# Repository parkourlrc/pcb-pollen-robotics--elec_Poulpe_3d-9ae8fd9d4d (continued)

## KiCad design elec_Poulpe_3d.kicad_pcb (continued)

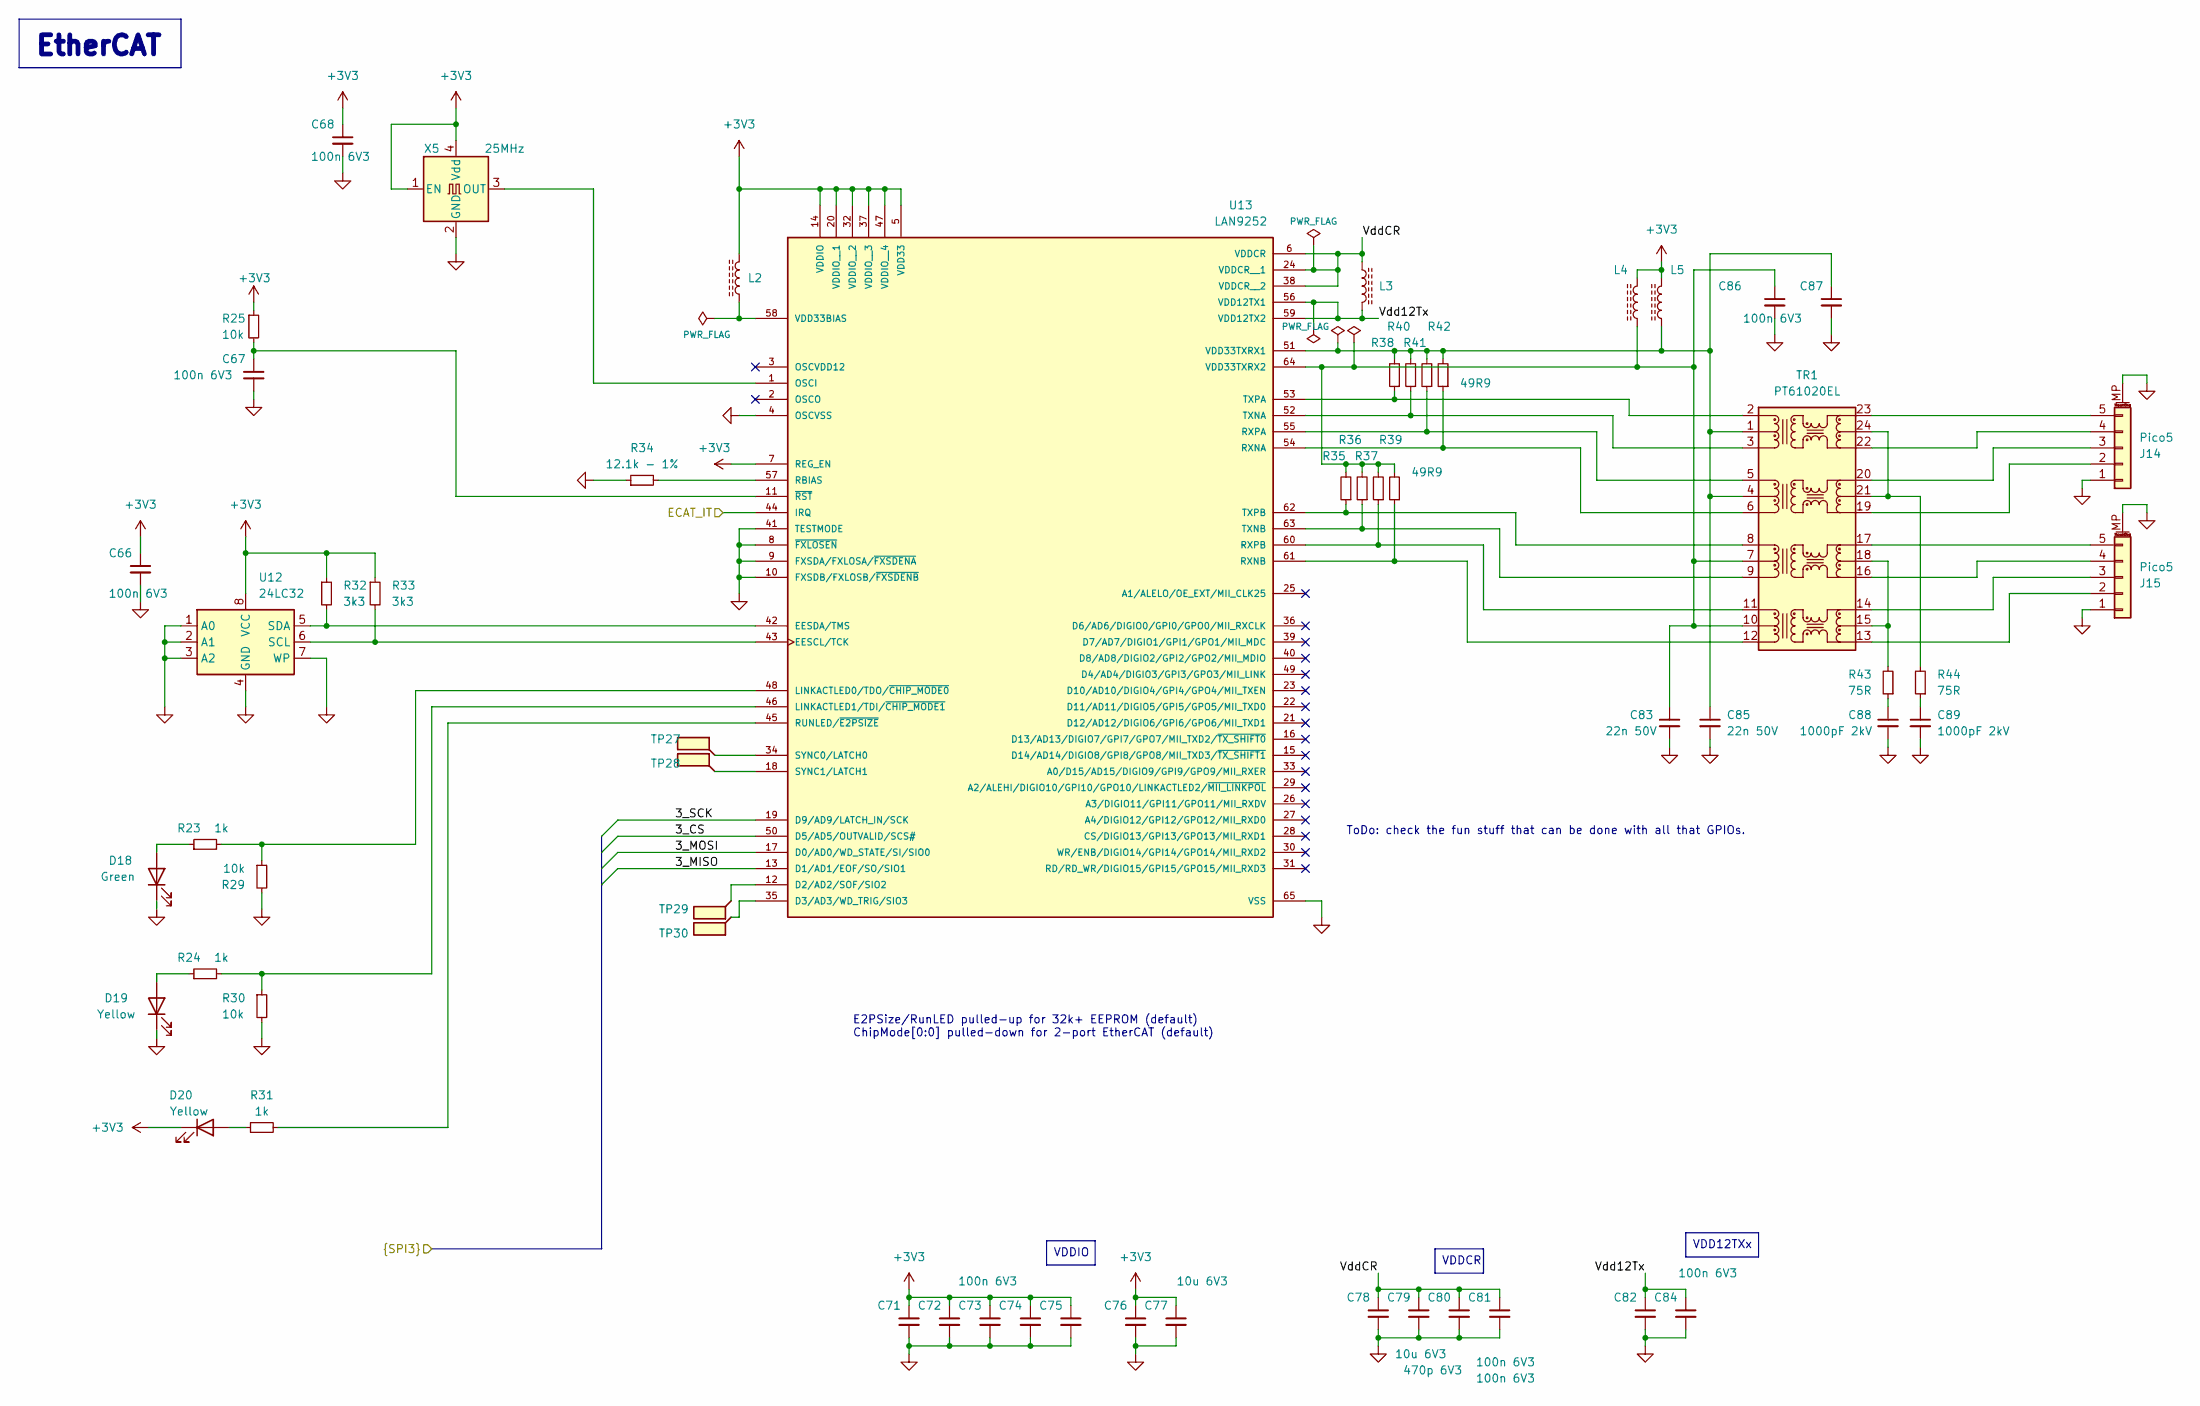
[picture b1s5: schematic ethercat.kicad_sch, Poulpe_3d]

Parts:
C66, C67, C68, C71, C72, C73, C74, C75, C80, C81, C82, C84, C86, C87: 100n 6V3; C_0402_1005Metric
C76, C77, C78: 10u 6V3; C_0402_1005Metric
C79: 470p 6V3; C_0402_1005Metric
C83, C85: 22n 50V; C_0603_1608Metric
C88, C89: 1000pF 2kV; C_1206_3216Metric
D18: Green; LED_0603_1608Metric
D19, D20: Yellow; LED_0603_1608Metric
J14, J15: Pico5; Molex_PicoBlade_53398-0571_1x05-1MP_P1.25mm_Vertical
L2, L3, L4, L5: FB; L_0603_1608Metric
R23, R24, R31: 1k; R_0402_1005Metric
R25, R29, R30: 10k; R_0402_1005Metric
R32, R33: 3k3; R_0402_1005Metric
R34: 12.1k - 1%; R_0603_1608Metric
R35, R36, R37, R38, R39, R40, R41, R42: 49R9; R_0402_1005Metric
R43, R44: 75R; R_0402_1005Metric
TP27, TP28, TP29, TP30: TestPoint_Flag; TestPoint_Line_0.2x0.8mm
TR1: PT61020EL; Bourns_PT61020EL
U12: 24LC32; SOIC-8_3.9x4.9mm_P1.27mm
U13: LAN9252; QFN-64-1EP_9x9mm_P0.5mm_EP6x6mm
X5: 25MHz; Abracon_ASE-4Pin_3.2x2.5mm

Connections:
/EtherCAT/3_CS: U13.50 (D5/AD5/OUTVALID/SCS#); also elsewhere on the board
/EtherCAT/3_MISO: U13.13 (D1/AD1/EOF/SO/SIO1); also elsewhere on the board
/EtherCAT/3_MOSI: U13.17 (D0/AD0/WD_STATE/SI/SIO0); also elsewhere on the board
/EtherCAT/3_SCK: U13.19 (D9/AD9/LATCH_IN/SCK); also elsewhere on the board
/EtherCAT/ECAT_IT: U13.44 (IRQ); also elsewhere on the board
/EtherCAT/Vdd12Tx: C82.1, C84.1, L3.2, U13.56 (VDD12TX1), U13.59 (VDD12TX2)
/EtherCAT/VddCR: C78.1, C79.1, C80.1, C81.1, L3.1, U13.6 (VDDCR), U13.24 (VDDCR__1), U13.38 (VDDCR__2)
unnamed: C88.1, R43.1
unnamed: C89.1, R44.1
unnamed: D18.2 (A), R23.1
unnamed: D19.2 (A), R24.1
unnamed: D20.2 (A), R31.1
unnamed: J14.2, TR1.19 (MX2-)
unnamed: J14.3, TR1.20 (MX2+)
unnamed: J14.4, TR1.22 (MX1-)
unnamed: J14.5, TR1.23 (MX1+)
unnamed: J15.2, TR1.13 (MX4-)
unnamed: J15.3, TR1.14 (MX4+)
unnamed: J15.4, TR1.16 (MX3-)
unnamed: J15.5, TR1.17 (MX3+)
unnamed: R44.2, TR1.21 (MCT2), TR1.24 (MCT1)
unnamed: R43.2, TR1.15 (MCT4), TR1.18 (MCT3)
unnamed: C85.1, C87.1, L5.1, R38.2, R40.2, R41.2, R42.2, TR1.1 (TCT1), TR1.4 (TCT2), U13.51 (VDD33TXRX1)
unnamed: C83.1, C86.1, L4.1, R35.2, R36.2, R37.2, R39.2, TR1.7 (TCT3), TR1.10 (TCT4), U13.64 (VDD33TXRX2)
unnamed: R38.1, TR1.2 (TD1+), U13.53 (TXPA)
unnamed: R40.1, TR1.3 (TD1-), U13.52 (TXNA)
unnamed: R41.1, TR1.5 (TD2+), U13.55 (RXPA)
unnamed: R42.1, TR1.6 (TD2-), U13.54 (RXNA)
unnamed: R35.1, TR1.8 (TD3+), U13.62 (TXPB)
unnamed: R36.1, TR1.9 (TD3-), U13.63 (TXNB)
unnamed: R37.1, TR1.11 (TD4+), U13.60 (RXPB)
unnamed: R39.1, TR1.12 (TD4-), U13.61 (RXNB)
unnamed: R33.2, U12.6 (SCL), U13.43 (EESCL/TCK)
unnamed: R32.2, U12.5 (SDA), U13.42 (EESDA/TMS)
unnamed: TP29.1, U13.12 (D2/AD2/SOF/SIO2)
unnamed: TP30.1, U13.35 (D3/AD3/WD_TRIG/SIO3)
unnamed: R23.2, R29.1, U13.48 (LINKACTLED0/TDO/~CHIP_MODE0)
unnamed: R24.2, R30.1, U13.46 (LINKACTLED1/TDI/~CHIP_MODE1)
unnamed: U13.1 (OSCI), X5.3 (OUT)
unnamed: R34.2, U13.57 (RBIAS)
unnamed: R31.2, U13.45 (RUNLED/~E2PSIZE)
unnamed: TP27.1, U13.34 (SYNC0/LATCH0)
unnamed: TP28.1, U13.18 (SYNC1/LATCH1)
unnamed: L2.1, U13.58 (VDD33BIAS)
unnamed: C67.1, R25.2, U13.11 (~RST)

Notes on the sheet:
VDDIO
EtherCAT
VDD12TXx
VDDCR
E2PSize/RunLED pulled-up for 32k+ EEPROM (default) ChipMode[0:0] pulled-down for 2-port EtherCAT (default)
ToDo: check the fun stuff that can be done with all that GPIOs.

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
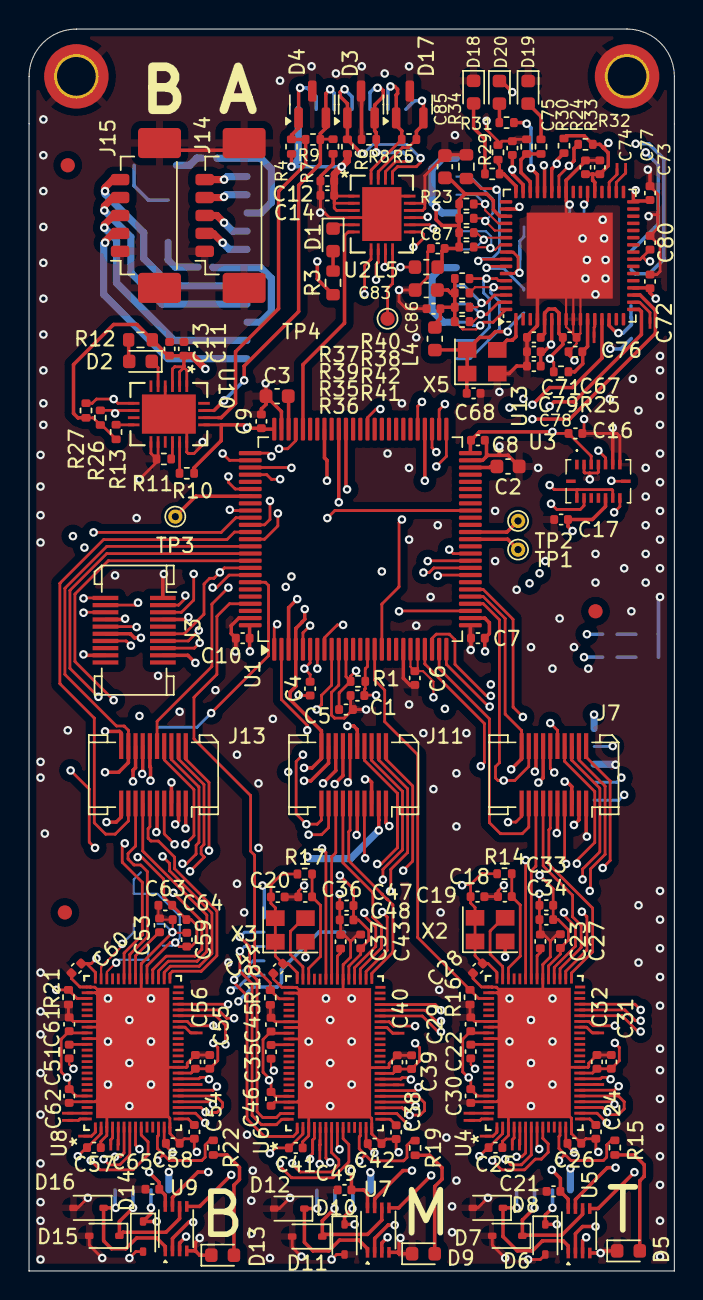
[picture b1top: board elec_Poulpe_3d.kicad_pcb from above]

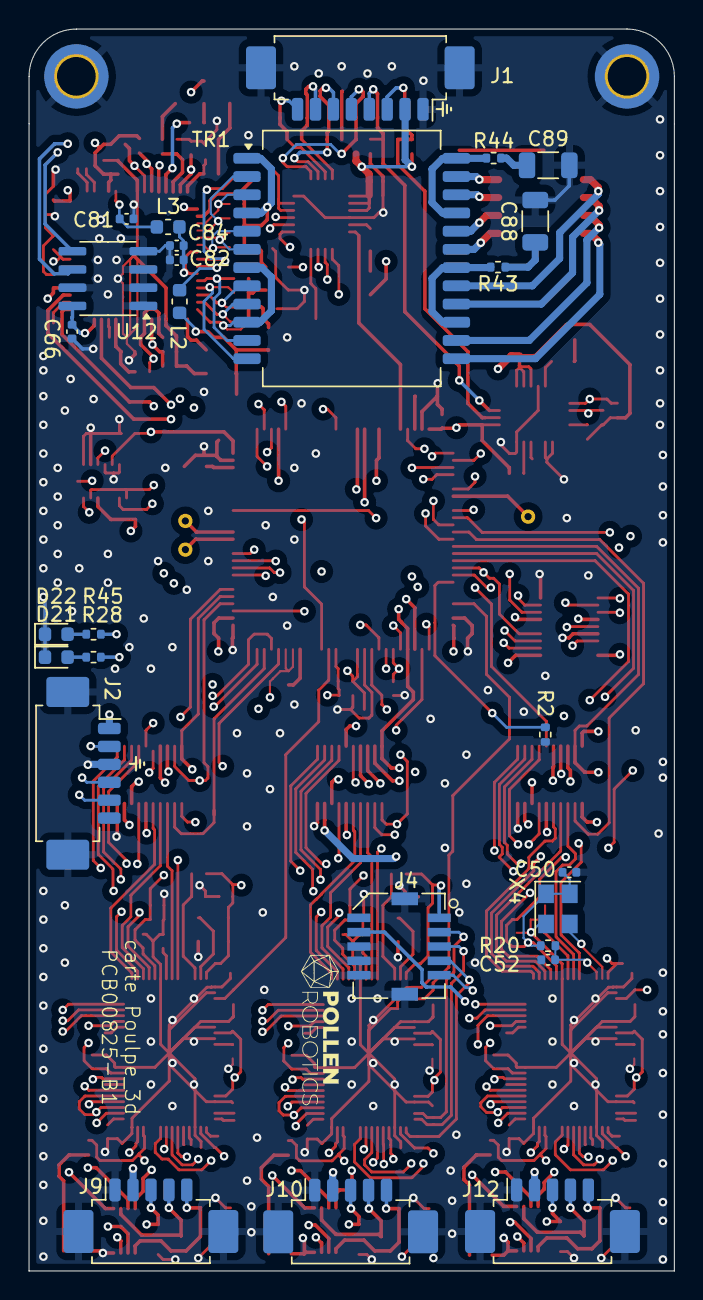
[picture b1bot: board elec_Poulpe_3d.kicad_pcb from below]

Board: 4 copper layers, 45.0 x 86.6 mm, 221 parts (28 on the bottom side), 209 nets.

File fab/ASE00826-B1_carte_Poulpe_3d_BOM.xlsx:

ASE00826 | B1 | Poulpe_3d | 45590
Ref. | Value | Description | Quantity | Man. | Man. Ref.
C1, C4, C5, C6, C7, C8, C9, C10, C16, C17, C18, C19, C20, C21, C22, C23, C24, C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 | 100n 6V3 | Capa 0402 | 63 | Eurocircuit | GPC0402104
C2, C3 | 2.2u 6V3 | Capa 0603 | 2 | Murata | GRM188R71A225KE15D
C11, C12 | 4.7uF 6V3 | Capa 0402 | 2 | Eurocircuit | GPC0402475-6.3
C13, C14 | 1uF 6V3 | Capa 0402 | 2 | Eurocircuit | GPC0402105-6.3
C32, C33, C40, C47, C56, C63 | 4.7u 6V3 | Capa 0603 | 6 | Eurocircuit | GPC0402475-6.3
C34, C48, C64 | 470n 6V3 | Capa 0603 | 3 | Eurocircuit | GPC0402474-25
C76, C77, C78 | 10u 6V3 | Capa 0402 | 3 | Eurocircuit | GPC0402106-6.3
C79 | 470p 6V3 | Capa 0402 | 1 | Eurocircuit | GPC0402471
C83, C85 | 22n 50V | Capa 0603 | 2 | Vishay | VJ0603Y223KXAAC
C88, C89 | 1000pF 2kV | Capa 1206 | 2 | Kemet | C1206C102KGRACTU
D3, D4, D17 | Dual TVS Diode |  | 3 | Rohm | MMBZ10VALYFHT116
D6, D7, D8, D10, D11, D12, D14, D15, D16 | D_Schottky | ESD Protection | 9 | On Semi | SD05T1G
D18, D21 | Green | Green LED 0603 | 2 | Wurth | 150060VS75000
D19, D20 | Yellow | Yellow LED 0603 | 2 | Wurth | 150060YS75020
D22 | Red | Red LED 0603 | 1 | Wurth | 150060RS75000
J1 | Pico8 |  | 1 | Molex | 53261-0871
J2 | Pico6 | Debug Connector | 1 | Molex | 53261-0671
J3, J7, J11, J13 | SlimStack Receptacle |  | 4 | Molex | 52991-0208
J4 | Trinamic_RTMI | DNP – FOC Prog Connec. | 1 | Hirose | DF20EF-10DP-1V(52)
J9, J10, J12 | Pico5 | Encoder Connec. | 3 | Molex | 53261-0571
J14, J15 | Pico5 | EtherCAT conn. | 2 | Molex | 53398-0571
L2, L3, L4, L5 | FB | Ferite Bead | 4 | Murata | BLM18EG221SN1D
R1, R14, R17, R20 | 100k | Res. 0402 | 4 | Eurocircuit | GPR0402100K
R2, R13, R16, R18, R21, R25, R29, R30 | 10k | Res. 0402 | 8 | Eurocircuit | GPR040210K
R4, R6, R7, R8 | 620R | Res. 0402 | 4 | Eurocircuit | GPR0402620R
R5, R9 | 120R | Res. 0402 | 2 | Eurocircuit | GPR0402120R
R10, R11 | 0R | Res. 0402 | 2 | Eurocircuit | GPR04020R
R23, R24, R31 | 1k | Res. 0402 | 3 | Eurocircuit | GPR04021K
R26, R27 | 4k7 | Res. 0402 | 2 | Eurocircuit | GPR04024K7
R28, R45 | 470R | Res. 0402 | 2 | Eurocircuit | GPR0402470R
R32, R33 | 3k3 | Res. 0402 | 2 | Eurocircuit | GPR04023K3
R34 | 12.1k - 1% | Res. 0603 | 1 | Yageo | RC0603FR-0712K1L
R35, R36, R37, R38, R39, R40, R41, R42 | 49R9 | Res. 0402 | 8 | Eurocircuit | GPR040251R
R43, R44 | 75R | Res. 0402 | 2 | Eurocircuit | GPR040275R
TP6, TP7, TP8, TP9, TP10, TP11, TP12, TP13, TP14, TP15, TP16, TP17, TP18, TP19,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 | TestPoint_Flag |  | 25
TR1 | PT61020EL | Ethernet Transformer | 1 | Bourns | PT61020EL
U1 | STM32H742/3VxTx | uC | 1 | ST Micro | STM32H743VGT6
U2 | LTC4332 | SPI to Differential Link | 1 | ADI | LTC4332CUFD#PBF
U3 | BMI088 | Inertial Measurement Unit | 1 | Bosch Sensortec | BMI088
U4, U6, U8 | TMC4671 |  | 3 | Trinamic / AD | TMC4671-LA
U5, U7, U9 | 74LVC3G17 | Schmidt Converter | 3 | TI | SN74LVC3G17DCUR
U10 | LTC4331 | I2C to Differential Link | 1 | ADI | LTC4331CUFD#PBF
U12 | 24LC32 | EEPROM 4k x 8bits | 1 | Microchip | 24LC32A/SN
U13 | LAN9252 | EtherCAT Slave Ctl. | 1 | Microchip | LAN9252/ML
X2, X3, X4, X5 | 25MHz | Oscillator | 4 | Abracon | ASE-25.000MHZ-L-C-T

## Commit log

2024-05-23 [init] Initial commit.
2024-05-24 [update] First sch.
2024-05-24 [update] Imported components OK.
2024-05-27 [update] Switching to layout replicate.
2024-05-27 [update] Issue with copying sheets
2024-05-27 [update] Replicate layout will fit.
2024-05-28 [update] FOC routed + layout replication.
2024-06-01 [update] Swapped the EtherCAT back to Poulpe.
2024-06-03 [update] Moving Sensors to Ventouse_3d
2024-06-03 [update] Schematic update ok
2024-06-04 [fixed] Stackable connec. positions.
2024-06-05 [update] Fully routed.
2024-06-05 [update] ERC OK, silk OK
2024-06-06 [update] Minor mechanical changes.
2024-08-21 [update] Todo list
2024-09-18 [fix] Shifting components for mec requirements. -> A2-RC1
2024-10-25 [update] going to B1, ERC OK for both SCH/PCB
2024-10-25 [update] Release B1!
2024-11-26 [fixed] still B1: small shift of both EtherCAT connectors.
2025-09-23 [update] Adding fab folder (sch, gerbers).
